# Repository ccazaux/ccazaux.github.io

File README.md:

# Portail pédagogique — Mes cours

Ce dossier est un exemple prêt à publier avec **GitHub Pages**.

## Structure

- `index.html` : portail avec arborescence, recherche et lecteur intégré.
- `1-numeration/` : exemple de cours Markdown, démonstration HTML, TP et TD PDF.
- `2-electricite/` et `3-mecanique/` : autres matières d'exemple.

## Prévisualiser sur votre ordinateur

Ouvrez `index.html` dans un navigateur. Pour tester le chargement des fichiers Markdown, il est préférable d'utiliser un petit serveur local (par exemple l'extension Live Server de Visual Studio Code), car certains navigateurs bloquent `fetch()` depuis un fichier local.

## Publier sur GitHub Pages

1. Créez un dépôt GitHub public, par exemple `mes-cours`.
2. Envoyez **tout le contenu** de ce dossier dans le dépôt (pas seulement `index.html`).
3. Dans GitHub : **Settings → Pages**.
4. Dans **Build and deployment**, choisissez **Deploy from a branch**.
5. Choisissez la branche `main` et le dossier `/ (root)`, puis enregistrez.
6. Après quelques minutes, GitHub affichera l'adresse du site dans la section Pages.

Votre portail sera accessible à une adresse du type `https://VOTRE-PSEUDO.github.io/mes-cours/`.

## Ajouter une matière

1. Créez un dossier, par exemple `4-optique/`.
2. Ajoutez vos fichiers : `Cours.md`, `demo.html`, `TP/TP1.pdf`, `TD/TD1.pdf`, etc.
3. Ouvrez `index.html` et ajoutez une entrée dans le tableau `courses` du script JavaScript, en suivant les exemples existants.
4. Envoyez les modifications sur GitHub.

## Formats pris en charge par le portail

- **Markdown (`.md`)** : rendu en lecture dans la page (le portail utilise la bibliothèque Marked chargée depuis un CDN). Un accès au réseau est nécessaire pour cette bibliothèque.
- **HTML (`.html`)** : affichage intégré dans un cadre isolé, ou ouverture dans un nouvel onglet.
- **PDF (`.pdf`)** : affichage intégré selon le navigateur, avec un lien de téléchargement.
- **ODT / ODS / ODP et autres formats** : ajoutez-les comme fichiers téléchargeables. Leur affichage direct dans le navigateur n'est pas garanti.

## Important : accès public

Avec un dépôt public et GitHub Pages, les fichiers et le site sont accessibles publiquement. Ne publiez pas de données personnelles, de copies d'élèves, de corrigés réservés ou de documents soumis à des restrictions de diffusion.

Les liens `download` invitent le navigateur à télécharger le fichier ; selon le navigateur et le type de fichier, certains PDF peuvent néanmoins s'ouvrir dans un nouvel onglet. Le fichier reste téléchargeable depuis GitHub.

## Détection automatique des documents

Le portail lit automatiquement l’arborescence du dépôt public via l’API GitHub. Après avoir ajouté un dossier ou un fichier et validé les changements, actualisez le site : les nouveaux éléments apparaissent dans le menu sans modifier `index.html`. Les fichiers Markdown (`.md`), HTML (`.html`) et PDF (`.pdf`) sont reconnus automatiquement ; les autres fichiers sont proposés au téléchargement.

**Important :** le dépôt doit être public pour que l’API GitHub puisse lire son contenu sans connexion. Sur une adresse GitHub Pages standard (`https://proprietaire.github.io/nom-du-depot/`), le propriétaire et le dépôt sont détectés automatiquement. Si vous utilisez un domaine personnalisé, renseignez `repoOwner` et `repoName` au début du script dans `index.html`.

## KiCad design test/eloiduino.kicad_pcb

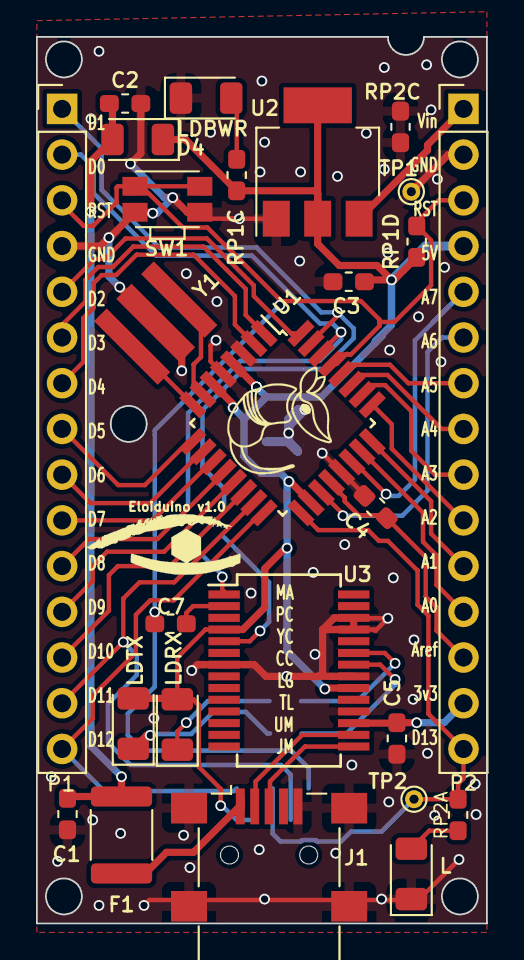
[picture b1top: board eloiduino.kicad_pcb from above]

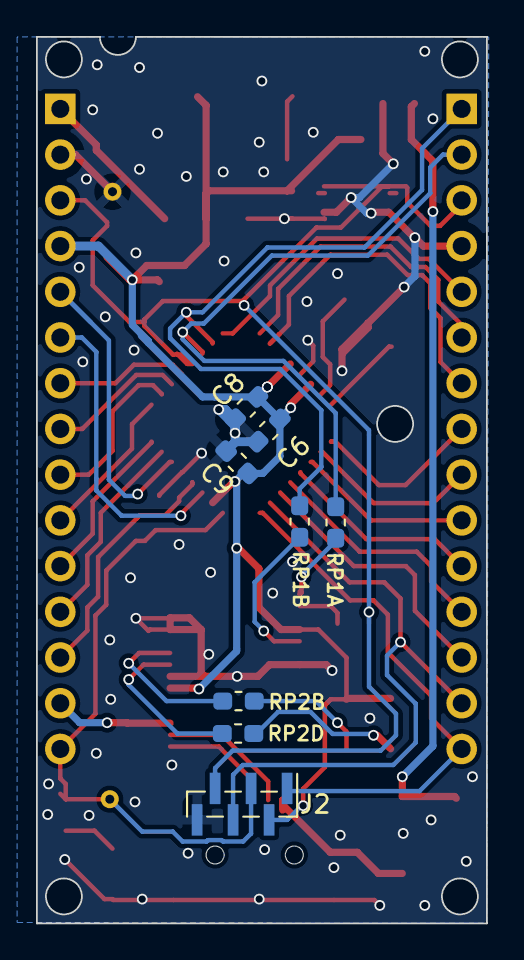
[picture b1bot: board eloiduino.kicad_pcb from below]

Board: 2 copper layers, 25.0 x 49.2 mm, 34 parts (8 on the bottom side), 43 nets.

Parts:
C1, C6: 4,7uF; C_0603_1608Metric_Pad1.05x0.95mm_HandSolder
C2, C4, C5, C7: 100nF; C_0603_1608Metric_Pad1.05x0.95mm_HandSolder
C3, C8, C9: 1uF; C_0603_1608Metric_Pad1.05x0.95mm_HandSolder
D4: D; LED_1206_3216Metric
F1: Fuse_Small; Fuse_1812_4532Metric
J1: USB_B_Mini; USB_Mini-B_Lumberg_2486_01_Horizontal
J2: Conn_02x03; PinHeader_1x06_P1.00mm_Vertical_SMD_Pin1Left
L: green; LED_1206_3216Metric
LDPWR: green; LED_1206_3216Metric
LDRX: Green; LED_1206_3216Metric
LDTX: Red; LED_1206_3216Metric
P1: Digital; PinHeader_1x15_P2.54mm_Vertical
P2: Analog; PinHeader_1x15_P2.54mm_Vertical
RP1A, RP1B, RP1C, RP1D, RP2A, RP2B, RP2C, RP2D: 1k; R_0603_1608Metric_Pad1.05x0.95mm_HandSolder
SW1: SW_DIP_x01; SW_SPST_EVQP7A
TP1: GND; TestPoint_THTPad_D1.0mm_Drill0.5mm
TP2: LED; TestPoint_THTPad_D1.0mm_Drill0.5mm
U1: ATmega328P-AU; TQFP-32_7x7mm_P0.8mm
U2: LM1117-5.0; SOT-223-3_TabPin2
U3: FT232RL; SSOP-28_5.3x10.2mm_P0.65mm
Y1: Resonator; Resonnator_SMD_test

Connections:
+3V3: C5.2, P2.14, U3.17
+5V: C3.1, C6.2, C8.2, C9.2, D4.1, J2.2, LDRX.2, LDTX.2, P2.4, RP1C.1, RP1D.1, U1.4, U1.6, U1.18, U2.2, U3.4, U3.20
/A0: P2.12, U1.23
/A1: P2.11, U1.24
/A2: P2.10, U1.25
/A3: P2.9, U1.26
/A4: P2.8, U1.27
/A5: P2.7, U1.28
/A6: P2.6, U1.19
/A7: P2.5, U1.22
/AREF: C4.1, P2.13, U1.20
/D0: P1.2, RP1A.1, U1.30
/D1: P1.1, RP1B.1, U1.31
/D2: P1.5, U1.32
/D3: P1.6, U1.1
/D4: P1.7, U1.2
/D5: P1.8, U1.9
/D6: P1.9, U1.10
/D7: P1.10, U1.11
/D8: P1.11, U1.12
/D9: P1.12, U1.13
/D10: P1.13, U1.14
/D11: J2.4, P1.14, U1.15
/D12: J2.1, P1.15, U1.16
/D13: J2.3, P2.15, RP2A.1, TP2.1, U1.17
/RESET: C7.1, J2.5, P1.3, P2.3, RP1D.2, SW1.1, U1.29
/RX: RP1A.2, U3.1
/TX: RP1B.2, U3.5
/USBD+: J1.3, U3.15
/USBD-: J1.2, U3.16
/Vin: P2.1, U2.3
GND: C1.2, C2.2, C3.2, C4.2, C5.1, C6.1, C8.1, C9.1, J1.5, J1.6, J2.6, L.1, LDPWR.1, P1.4, P2.2, RP2C.1, RP2C.2, SW1.2, TP1.1, U1.3, U1.5, U1.21, U2.1, U3.7, U3.18, U3.21, U3.25, U3.26, Y1.2
unnamed: C7.2, U3.2
unnamed: F1.1, J1.1
unnamed: L.2, RP2A.2
unnamed: LDPWR.2, RP1C.2
unnamed: LDRX.1, RP2B.2
unnamed: LDTX.1, RP2D.2
unnamed: RP2B.1, U3.23
unnamed: RP2D.1, U3.22
unnamed: U1.7, Y1.3
unnamed: U1.8, Y1.1
VBUS: C1.1, C2.1, D4.2, F1.2
